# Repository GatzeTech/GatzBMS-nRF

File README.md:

# GatzBMS-nRF

Short explanation for now.

I was a bit annoyed with the Chinese BMS's that you don't have any feedback on the status of for example balancing or why it cutt off power. Once I was in the middle of nowhere when my eBike suddenly stopped and physically I'm really dependant on the electric system so for example in such case, I want to read out the voltage's and decide for myself if it is still safe to go on. If I have to bike myself physically longer distance's (5 km) I can be sick for day's. In that case one cell group was a little bit off, but still in the safe range, in that case I want to be able to put the mosfets on again for example via bluetooth.

So I came up with the idea to design myself a BMS. The goal is to use simple components (also with the chip delivery problems in mind) except for the microcontroller/Soc. It's a compromise between functionality, costs, availability, simplicity.

Design choice's I will discuss later.

At the moment I'm busy with the software.

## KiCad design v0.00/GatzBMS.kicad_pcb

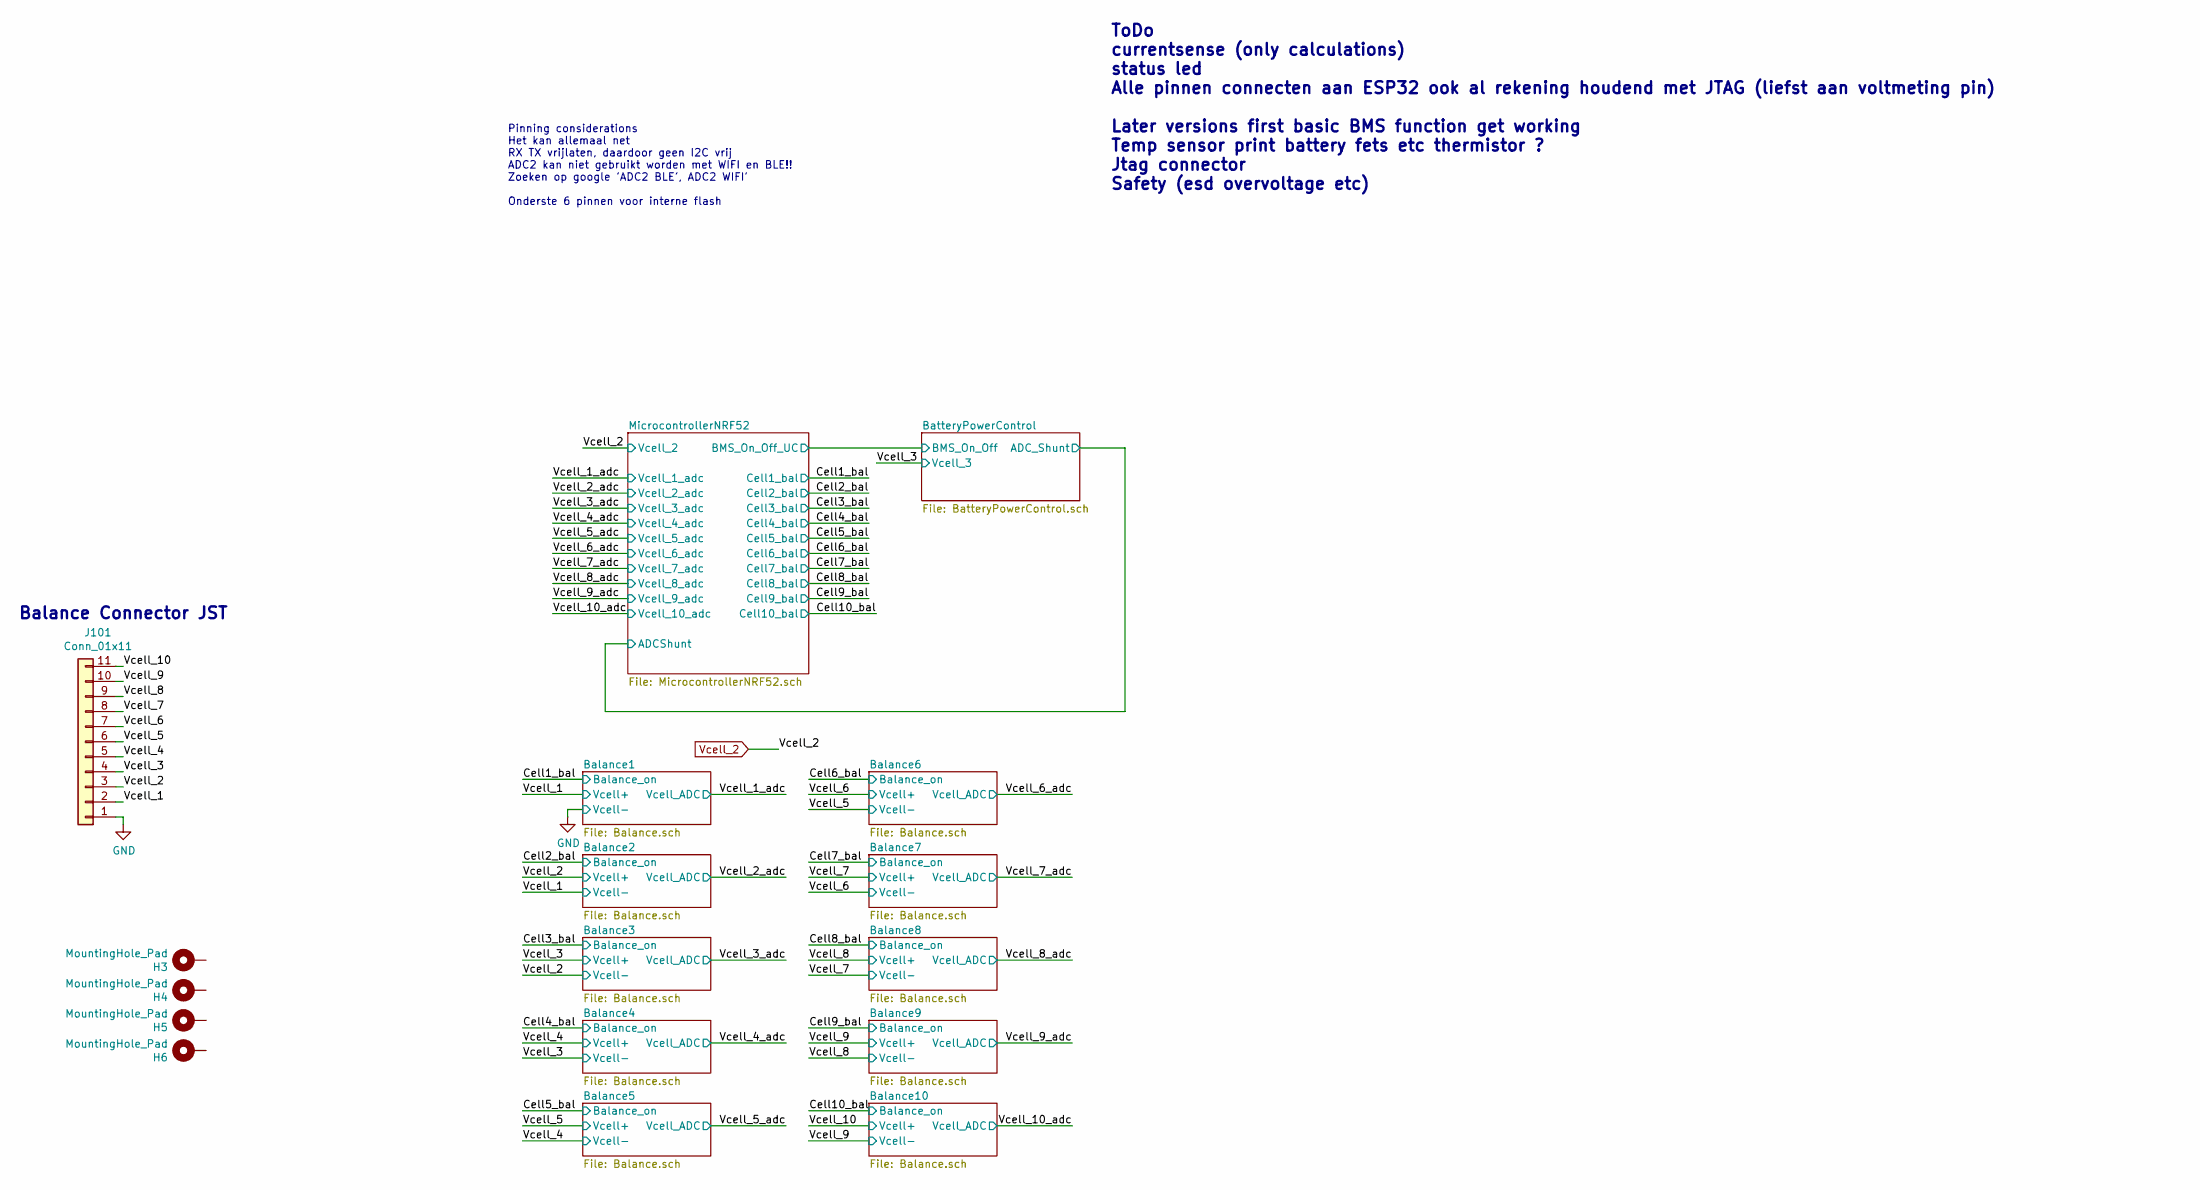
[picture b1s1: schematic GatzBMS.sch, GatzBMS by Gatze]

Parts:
H3, H4, H5, H6: MountingHole_Pad; MountingHole_3.2mm_M3_ISO7380_Pad_TopBottom
J101: Conn_01x11; JST_PH_S11B-PH-K_1x11_P2.00mm_Horizontal

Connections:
/Vcell_1: J101.2; also elsewhere on the board
/Vcell_3: J101.4; also elsewhere on the board
/Vcell_4: J101.5; also elsewhere on the board
/Vcell_5: J101.6; also elsewhere on the board
/Vcell_6: J101.7; also elsewhere on the board
/Vcell_7: J101.8; also elsewhere on the board
/Vcell_8: J101.9; also elsewhere on the board
/Vcell_9: J101.10; also elsewhere on the board
/Vcell_10: J101.11; also elsewhere on the board
GND: J101.1; also elsewhere on the board
Vcell_2: J101.3; also elsewhere on the board

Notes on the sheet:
Balance Connector JST
ToDo currentsense (only calculations) status led Alle pinnen connecten aan ESP32 ook al rekening houdend met JTAG (liefst aan voltmeting pin) Later versions first basic BMS function get working Temp sensor print battery fets etc thermistor ? Jtag connector Safety (esd overvoltage etc)
Pinning considerations Het kan allemaal net RX TX vrijlaten, daardoor geen I2C vrij ADC2 kan niet gebruikt worden met WIFI en BLE!! Zoeken op google 'ADC2 BLE', ADC2 WIFI' Onderste 6 pinnen voor interne flash

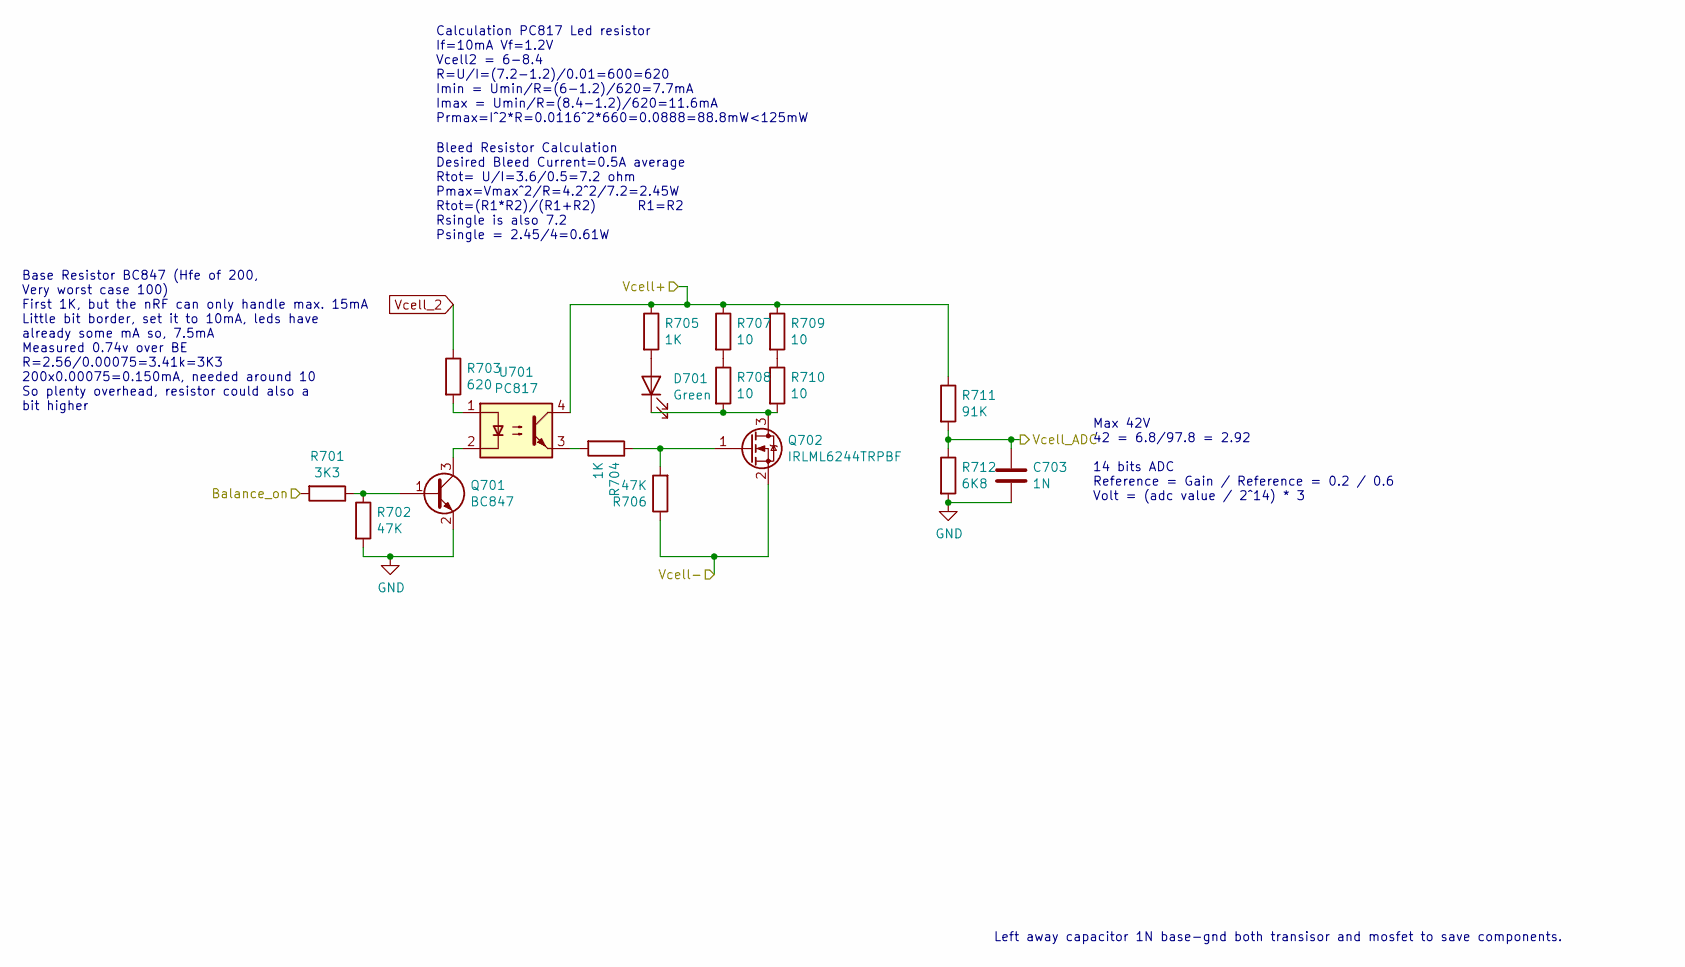
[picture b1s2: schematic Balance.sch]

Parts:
C203: 1N; C_0805_2012Metric
D201: Green; LED_0805_2012Metric_Pad1.15x1.40mm_HandSolder
Q201: BC847; SOT-23
Q202: IRLML6244TRPBF; SOT-23
R201: 3K3; R_0805_2012Metric_Pad1.20x1.40mm_HandSolder
R202, R206: 47K; R_0805_2012Metric_Pad1.20x1.40mm_HandSolder
R203: 620; R_0805_2012Metric_Pad1.20x1.40mm_HandSolder
R204, R205: 1K; R_0805_2012Metric_Pad1.20x1.40mm_HandSolder
R207, R208, R209, R210: 10; R_2512_6332Metric_Pad1.40x3.35mm_HandSolder
R211: 91K; R_0805_2012Metric_Pad1.20x1.40mm_HandSolder
R212: 6K8; R_0805_2012Metric_Pad1.20x1.40mm_HandSolder
U201: PC817; SMDIP-4_W9.53mm_Clearance8mm

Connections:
/Cell1_bal: R201.2; also elsewhere on the board
/Vcell_1: R205.1, R207.1, R209.1, R211.1, U201.4; also elsewhere on the board
/Vcell_1_adc: C203.1, R211.2, R212.1; also elsewhere on the board
GND: C203.2, Q201.2 (E), Q202.2 (S), R202.2, R206.1, R212.2; also elsewhere on the board
unnamed: D201.1 (K), Q202.3 (D), R208.2, R210.2
unnamed: D201.2 (A), R205.2
unnamed: Q201.1 (B), R201.1, R202.1
unnamed: Q201.3 (C), U201.2
unnamed: Q202.1 (G), R204.1, R206.2
unnamed: R203.2, U201.1
unnamed: R204.2, U201.3
unnamed: R207.2, R208.1
unnamed: R209.2, R210.1
Vcell_2: R203.1; also elsewhere on the board

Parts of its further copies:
C303, C403, C503, C603, C703, C803, C903, C1003, C1103: 1N; C_0805_2012Metric
D301, D401, D501, D601, D701, D801, D901, D1001, D1101: Green; LED_0805_2012Metric_Pad1.15x1.40mm_HandSolder
Q301, Q401, Q501, Q601, Q701, Q801, Q901, Q1001, Q1101: BC847; SOT-23
Q302, Q402, Q502, Q602, Q702, Q802, Q902, Q1002, Q1102: IRLML6244TRPBF; SOT-23
R301, R401, R501, R601, R701, R801, R901, R1001, R1101: 3K3; R_0805_2012Metric_Pad1.20x1.40mm_HandSolder
R302, R306, R402, R406, R502, R506, R602, R606, R702, R706, R802, R806, R902, R906, R1002, R1006, R1102, R1106: 47K; R_0805_2012Metric_Pad1.20x1.40mm_HandSolder
R303, R403, R503, R603, R703, R803, R903, R1003, R1103: 620; R_0805_2012Metric_Pad1.20x1.40mm_HandSolder
R304, R305, R404, R405, R504, R505, R604, R605, R704, R705, R804, R805, R904, R905, R1004, R1005, R1104, R1105: 1K; R_0805_2012Metric_Pad1.20x1.40mm_HandSolder
R307, R308, R309, R310, R407, R408, R409, R410, R507, R508, R509, R510, R607, R608, R609, R610, R707, R708, R709, R710, R807, R808, R809, R810, R907, R908, R909, R910, R1007, R1008, R1009, R1010, R1107, R1108, R1109, R1110: 10; R_2512_6332Metric_Pad1.40x3.35mm_HandSolder
R311, R411, R511, R611, R711, R811, R911, R1011, R1111: 91K; R_0805_2012Metric_Pad1.20x1.40mm_HandSolder
R312, R412, R512, R612, R712, R812, R912, R1012, R1112: 6K8; R_0805_2012Metric_Pad1.20x1.40mm_HandSolder
U301, U401, U501, U601, U701, U801, U901, U1001, U1101: PC817; SMDIP-4_W9.53mm_Clearance8mm

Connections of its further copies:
/Cell2_bal: R301.2; also elsewhere on the board
/Cell3_bal: R401.2; also elsewhere on the board
/Cell4_bal: R501.2; also elsewhere on the board
/Cell5_bal: R601.2; also elsewhere on the board
/Cell6_bal: R701.2; also elsewhere on the board
/Cell7_bal: R801.2; also elsewhere on the board
/Cell8_bal: R901.2; also elsewhere on the board
/Cell9_bal: R1001.2; also elsewhere on the board
/Cell10_bal: R1101.2; also elsewhere on the board
/Vcell_1: Q302.2 (S), R306.1; also elsewhere on the board
/Vcell_2_adc: C303.1, R311.2, R312.1; also elsewhere on the board
/Vcell_3: Q502.2 (S), R405.1, R407.1, R409.1, R411.1, R506.1, U401.4; also elsewhere on the board
/Vcell_3_adc: C403.1, R411.2, R412.1; also elsewhere on the board
/Vcell_4: Q602.2 (S), R505.1, R507.1, R509.1, R511.1, R606.1, U501.4; also elsewhere on the board
/Vcell_4_adc: C503.1, R511.2, R512.1; also elsewhere on the board
/Vcell_5: Q702.2 (S), R605.1, R607.1, R609.1, R611.1, R706.1, U601.4; also elsewhere on the board
/Vcell_5_adc: C603.1, R611.2, R612.1; also elsewhere on the board
/Vcell_6: Q802.2 (S), R705.1, R707.1, R709.1, R711.1, R806.1, U701.4; also elsewhere on the board
/Vcell_6_adc: C703.1, R711.2, R712.1; also elsewhere on the board
/Vcell_7: Q902.2 (S), R805.1, R807.1, R809.1, R811.1, R906.1, U801.4; also elsewhere on the board
/Vcell_7_adc: C803.1, R811.2, R812.1; also elsewhere on the board
/Vcell_8: Q1002.2 (S), R905.1, R907.1, R909.1, R911.1, R1006.1, U901.4; also elsewhere on the board
/Vcell_8_adc: C903.1, R911.2, R912.1; also elsewhere on the board
/Vcell_9: Q1102.2 (S), R1005.1, R1007.1, R1009.1, R1011.1, R1106.1, U1001.4; also elsewhere on the board
/Vcell_9_adc: C1003.1, R1011.2, R1012.1; also elsewhere on the board
/Vcell_10: R1105.1, R1107.1, R1109.1, R1111.1, U1101.4; also elsewhere on the board
/Vcell_10_adc: C1103.1, R1111.2, R1112.1; also elsewhere on the board
GND: C303.2, C403.2, C503.2, C603.2, C703.2, C803.2, C903.2, C1003.2, C1103.2, Q301.2 (E), Q401.2 (E), Q501.2 (E), Q601.2 (E), Q701.2 (E), Q801.2 (E), Q901.2 (E), Q1001.2 (E), Q1101.2 (E), R302.2, R312.2, R402.2, R412.2, R502.2, R512.2, R602.2, R612.2, R702.2, R712.2, R802.2, R812.2, R902.2, R912.2, R1002.2, R1012.2, R1102.2, R1112.2; also elsewhere on the board
unnamed: D301.1 (K), Q302.3 (D), R308.2, R310.2
unnamed: D301.2 (A), R305.2
unnamed: D401.1 (K), Q402.3 (D), R408.2, R410.2
unnamed: D401.2 (A), R405.2
unnamed: D501.1 (K), Q502.3 (D), R508.2, R510.2
unnamed: D501.2 (A), R505.2
unnamed: D601.1 (K), Q602.3 (D), R608.2, R610.2
unnamed: D601.2 (A), R605.2
unnamed: D701.1 (K), Q702.3 (D), R708.2, R710.2
unnamed: D701.2 (A), R705.2
unnamed: D801.1 (K), Q802.3 (D), R808.2, R810.2
unnamed: D801.2 (A), R805.2
unnamed: D901.1 (K), Q902.3 (D), R908.2, R910.2
unnamed: D901.2 (A), R905.2
unnamed: D1001.1 (K), Q1002.3 (D), R1008.2, R1010.2
unnamed: D1001.2 (A), R1005.2
unnamed: D1101.1 (K), Q1102.3 (D), R1108.2, R1110.2
unnamed: D1101.2 (A), R1105.2
unnamed: Q301.1 (B), R301.1, R302.1
unnamed: Q301.3 (C), U301.2
unnamed: Q302.1 (G), R304.1, R306.2
unnamed: Q401.1 (B), R401.1, R402.1
unnamed: Q401.3 (C), U401.2
unnamed: Q402.1 (G), R404.1, R406.2
unnamed: Q501.1 (B), R501.1, R502.1
unnamed: Q501.3 (C), U501.2
unnamed: Q502.1 (G), R504.1, R506.2
unnamed: Q601.1 (B), R601.1, R602.1
unnamed: Q601.3 (C), U601.2
unnamed: Q602.1 (G), R604.1, R606.2
unnamed: Q701.1 (B), R701.1, R702.1
unnamed: Q701.3 (C), U701.2
unnamed: Q702.1 (G), R704.1, R706.2
unnamed: Q801.1 (B), R801.1, R802.1
unnamed: Q801.3 (C), U801.2
unnamed: Q802.1 (G), R804.1, R806.2
unnamed: Q901.1 (B), R901.1, R902.1
unnamed: Q901.3 (C), U901.2
unnamed: Q902.1 (G), R904.1, R906.2
unnamed: Q1001.1 (B), R1001.1, R1002.1
unnamed: Q1001.3 (C), U1001.2
unnamed: Q1002.1 (G), R1004.1, R1006.2
unnamed: Q1101.1 (B), R1101.1, R1102.1
unnamed: Q1101.3 (C), U1101.2
unnamed: Q1102.1 (G), R1104.1, R1106.2
unnamed: R303.2, U301.1
unnamed: R304.2, U301.3
unnamed: R307.2, R308.1
unnamed: R309.2, R310.1
unnamed: R403.2, U401.1
unnamed: R404.2, U401.3
unnamed: R407.2, R408.1
unnamed: R409.2, R410.1
unnamed: R503.2, U501.1
unnamed: R504.2, U501.3
unnamed: R507.2, R508.1
unnamed: R509.2, R510.1
unnamed: R603.2, U601.1
unnamed: R604.2, U601.3
unnamed: R607.2, R608.1
unnamed: R609.2, R610.1
unnamed: R703.2, U701.1
unnamed: R704.2, U701.3
unnamed: R707.2, R708.1
unnamed: R709.2, R710.1
unnamed: R803.2, U801.1
unnamed: R804.2, U801.3
unnamed: R807.2, R808.1
unnamed: R809.2, R810.1
unnamed: R903.2, U901.1
unnamed: R904.2, U901.3
unnamed: R907.2, R908.1
unnamed: R909.2, R910.1
unnamed: R1003.2, U1001.1
unnamed: R1004.2, U1001.3
unnamed: R1007.2, R1008.1
unnamed: R1009.2, R1010.1
unnamed: R1103.2, U1101.1
unnamed: R1104.2, U1101.3
unnamed: R1107.2, R1108.1
unnamed: R1109.2, R1110.1
Vcell_2: Q402.2 (S), R303.1, R305.1, R307.1, R309.1, R311.1, R403.1, R406.1, R503.1, R603.1, R703.1, R803.1, R903.1, R1003.1, R1103.1, U301.4; also elsewhere on the board

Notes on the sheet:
Calculation PC817 Led resistor If=10mA Vf=1.2V Vcell2 = 6-8.4 R=U/I=(7.2-1.2)/0.01=600=620 Imin = Umin/R=(6-1.2)/620=7.7mA Imax = Umin/R=(8.4-1.2)/620=11.6mA Prmax=I^2*R=0.0116^2*660=0.0888=88.8mW<125mW
Bleed Resistor Calculation Desired Bleed Current=0.5A average Rtot= U/I=3.6/0.5=7.2 ohm Pmax=Vmax^2/R=4.2^2/7.2=2.45W Rtot=(R1*R2)/(R1+R2) R1=R2 Rsingle is also 7.2 Psingle = 2.45/4=0.61W
Left away capacitor 1N base-gnd both transisor and mosfet to save components.
Base Resistor BC847 (Hfe of 200, Very worst case 100) First 1K, but the nRF can only handle max. 15mA Little bit border, set it to 10mA, leds have already some mA so, 7.5mA Measured 0.74v over BE R=2.56/0.00075=3.41k=3K3 200x0.00075=0.150mA, needed around 10 So plenty overhead, resistor could also 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
Max 42V 42 = 6.8/97.8 = 2.92 14 bits ADC Reference = Gain / Reference = 0.2 / 0.6 Volt = (adc value / 2^14) * 3

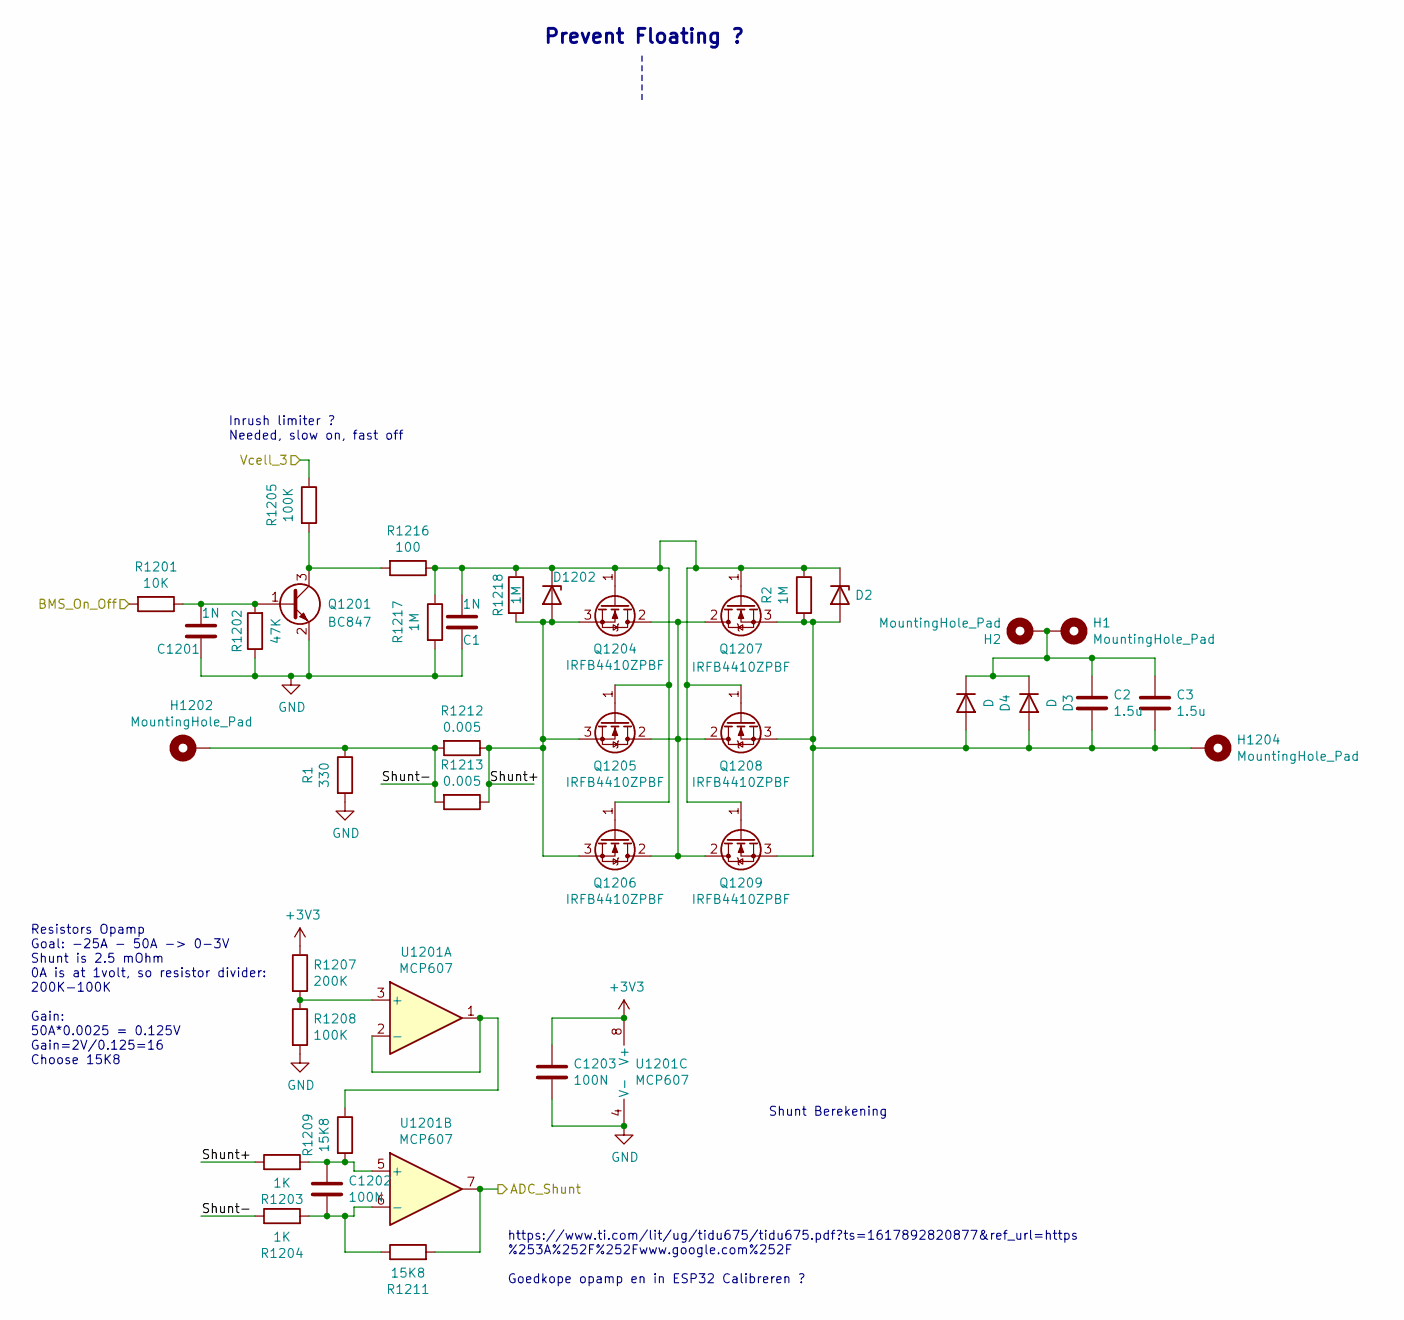
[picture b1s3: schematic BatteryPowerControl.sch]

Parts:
C1, C1201: 1N; C_0805_2012Metric_Pad1.18x1.45mm_HandSolder
C2, C3: 1.5u; C_1210_3225Metric_Pad1.33x2.70mm_HandSolder
C1202, C1203: 100N; C_0805_2012Metric
D2, D1202: Z1SMA15; D_SOD-523
D3, D4: D; D_SMA_Handsoldering
H1, H2, H1202, H1204: MountingHole_Pad; MountingHole_3.2mm_M3_ISO7380_Pad_TopBottom
Q1201: BC847; SOT-23
Q1204, Q1205, Q1206, Q1207, Q1208, Q1209: IRFB4410ZPBF; TO-220-3_Horizontal_TabDown_modified
R1: 330; R_0805_2012Metric_Pad1.20x1.40mm_HandSolder
R2, R1217, R1218: 1M; R_0805_2012Metric_Pad1.20x1.40mm_HandSolder
R1201: 10K; R_0805_2012Metric_Pad1.20x1.40mm_HandSolder
R1202: 47K; R_0805_2012Metric_Pad1.20x1.40mm_HandSolder
R1203, R1204: 1K; R_0805_2012Metric_Pad1.20x1.40mm_HandSolder
R1205, R1208: 100K; R_0805_2012Metric_Pad1.20x1.40mm_HandSolder
R1207: 200K; R_0805_2012Metric_Pad1.20x1.40mm_HandSolder
R1209, R1211: 15K8; R_0805_2012Metric_Pad1.20x1.40mm_HandSolder
R1212, R1213: 0.005; R_2512_6332Metric_Pad1.40x3.35mm_HandSolder
R1216: 100; R_0805_2012Metric_Pad1.20x1.40mm_HandSolder
U1201: MCP607; SOIC-8_3.9x4.9mm_P1.27mm

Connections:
+3V3: C1203.1, R1207.1, U1201.8 (V+); also elsewhere on the board
/BatteryPowerControl/BMS_On_Off: R1201.2; also elsewhere on the board
/BatteryPowerControl/Shunt+: D1202.2 (A), Q1204.3 (S), Q1205.3 (S), Q1206.3 (S), R1203.1, R1212.1, R1213.1, R1218.2
/BatteryPowerControl/Shunt-: H1202.1, R1.1, R1204.1, R1212.2, R1213.2
/MicrocontrollerNRF52/ADCShunt: R1211.2, U1201.7; also elsewhere on the board
/Vcell_3: R1205.1; also elsewhere on the board
GND: C1.2, C1201.2, C1203.2, Q1201.2 (E), R1.2, R1202.1, R1208.2, R1217.2, U1201.4 (V-); also elsewhere on the board
unnamed: C1.1, D2.1 (K), D1202.1 (K), Q1204.1 (G), Q1205.1 (G), Q1206.1 (G), Q1207.1 (G), Q1208.1 (G), Q1209.1 (G), R2.1, R1216.1, R1217.1, R1218.1
unnamed: C2.1, C3.1, D3.1 (K), D4.1 (K), H1.1, H2.1
unnamed: C2.2, C3.2, D2.2 (A), D3.2 (A), D4.2 (A), H1204.1, Q1207.3 (S), Q1208.3 (S), Q1209.3 (S), R2.2
unnamed: C1201.1, Q1201.1 (B), R1201.1, R1202.2
unnamed: C1202.1, R1203.2, R1209.2, U1201.5 (+)
unnamed: C1202.2, R1204.2, R1211.1, U1201.6 (-)
unnamed: Q1201.3 (C), R1205.2, R1216.2
unnamed: Q1204.2 (D), Q1205.2 (D), Q1206.2 (D), Q1207.2 (D), Q1208.2 (D), Q1209.2 (D)
unnamed: R1207.2, R1208.1, U1201.3 (+)
unnamed: R1209.1, U1201.1, U1201.2 (-)

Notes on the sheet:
https://www.ti.com/lit/ug/tidu675/tidu675.pdf?ts=1617892820877&ref_url=https %253A%252F%252Fwww.google.com%252F Goedkope opamp en in ESP32 Calibreren ?
Inrush limiter ? Needed, slow on, fast off
Prevent Floating ?
Shunt Berekening
Resistors Opamp Goal: -25A - 50A -> 0-3V Shunt is 2.5 mOhm 0A is at 1volt, so resistor divider: 200K-100K Gain: 50A*0.0025 = 0.125V Gain=2V/0.125=16 Choose 15K8

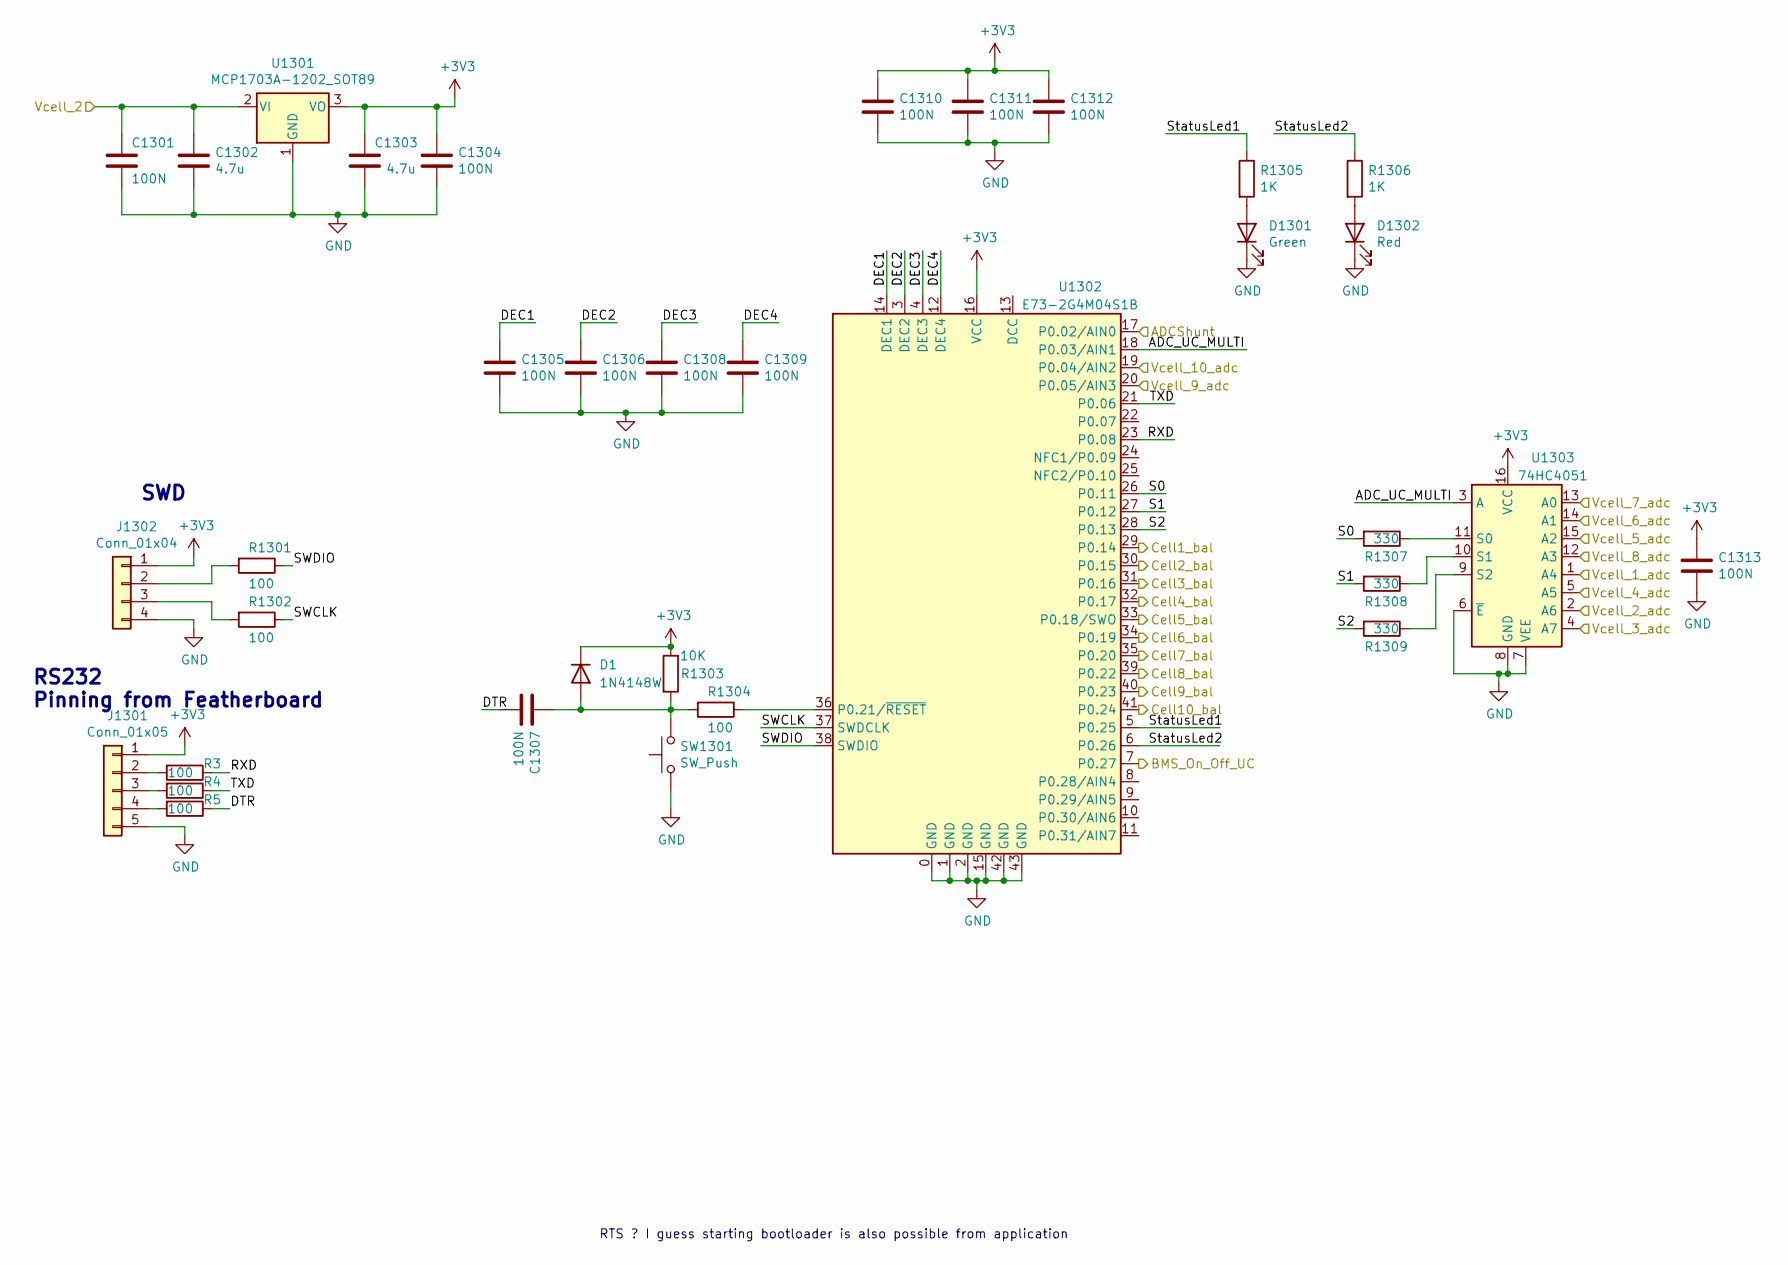
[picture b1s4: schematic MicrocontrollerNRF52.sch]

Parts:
C1301, C1304, C1305, C1306, C1307, C1308, C1309, C1310, C1311, C1312, C1313: 100N; C_0805_2012Metric
C1302, C1303: 4.7u; C_1210_3225Metric_Pad1.33x2.70mm_HandSolder
D1: 1N4148W; D_SOD-123
D1301: Green; LED_0805_2012Metric_Pad1.15x1.40mm_HandSolder
D1302: Red; LED_0805_2012Metric_Pad1.15x1.40mm_HandSolder
J1301: Conn_01x05; JST_PH_B5B-PH-K_1x05_P2.00mm_Vertical
J1302: Conn_01x04; JST_PH_B4B-PH-K_1x04_P2.00mm_Vertical
R3, R4, R5, R1301, R1302, R1304: 100; R_0805_2012Metric_Pad1.20x1.40mm_HandSolder
R1303: 10K; R_0805_2012Metric_Pad1.20x1.40mm_HandSolder
R1305, R1306: 1K; R_0805_2012Metric_Pad1.20x1.40mm_HandSolder
R1307, R1308, R1309: 330; R_0805_2012Metric_Pad1.20x1.40mm_HandSolder
SW1301: SW_Push; SW_Push_1P1T_NO_6x6mm_H9.5mm
U1301: MCP1703A-1202_SOT89; SOT-89-3
U1302: E73-2G4M04S1B
U1303: 74HC4051; SO-16_3.9x9.9mm_P1.27mm

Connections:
+3V3: C1303.1, C1304.1, C1310.1, C1311.1, C1312.1, C1313.1, D1.1 (K), J1301.1, J1302.1, R1303.2, U1301.3 (VO), U1302.16 (VCC), U1303.16 (VCC); also elsewhere on the board
/BatteryPowerControl/BMS_On_Off: U1302.7 (P0.27); also elsewhere on the board
/Cell1_bal: U1302.29 (P0.14); also elsewhere on the board
/Cell2_bal: U1302.30 (P0.15); also elsewhere on the board
/Cell3_bal: U1302.31 (P0.16); also elsewhere on the board
/Cell4_bal: U1302.32 (P0.17); also elsewhere on the board
/Cell5_bal: U1302.33 (P0.18/SWO); also elsewhere on the board
/Cell6_bal: U1302.34 (P0.19); also elsewhere on the board
/Cell7_bal: U1302.35 (P0.20); also elsewhere on the board
/Cell8_bal: U1302.39 (P0.22); also elsewhere on the board
/Cell9_bal: U1302.40 (P0.23); also elsewhere on the board
/Cell10_bal: U1302.41 (P0.24); also elsewhere on the board
/MicrocontrollerNRF52/ADCShunt: U1302.17 (P0.02/AIN0); also elsewhere on the board
/MicrocontrollerNRF52/ADC_UC_MULTI: U1302.18 (P0.03/AIN1), U1303.3 (A)
/MicrocontrollerNRF52/DEC1: C1305.1, U1302.14 (DEC1)
/MicrocontrollerNRF52/DEC2: C1306.1, U1302.3 (DEC2)
/MicrocontrollerNRF52/DEC3: C1308.1, U1302.4 (DEC3)
/MicrocontrollerNRF52/DEC4: C1309.1, U1302.12 (DEC4)
/MicrocontrollerNRF52/DTR: C1307.2, R5.1
/MicrocontrollerNRF52/RXD: R3.1, U1302.23 (P0.08)
/MicrocontrollerNRF52/S0: R1307.2, U1302.26 (P0.11)
/MicrocontrollerNRF52/S1: R1308.2, U1302.27 (P0.12)
/MicrocontrollerNRF52/S2: R1309.2, U1302.28 (P0.13)
/MicrocontrollerNRF52/SWCLK: R1302.1, U1302.37 (SWDCLK)
/MicrocontrollerNRF52/SWDIO: R1301.1, U1302.38 (SWDIO)
/MicrocontrollerNRF52/StatusLed1: R1305.1, U1302.5 (P0.25)
/MicrocontrollerNRF52/StatusLed2: R1306.1, U1302.6 (P0.26)
/MicrocontrollerNRF52/TXD: R4.1, U1302.21 (P0.06)
/Vcell_1_adc: U1303.1 (A4); also elsewhere on the board
/Vcell_2_adc: U1303.2 (A6); also elsewhere on the board
/Vcell_3_adc: U1303.4 (A7); also elsewhere on the board
/Vcell_4_adc: U1303.5 (A5); also elsewhere on the board
/Vcell_5_adc: U1303.15 (A2); also elsewhere on the board
/Vcell_6_adc: U1303.14 (A1); also elsewhere on the board
/Vcell_7_adc: U1303.13 (A0); also elsewhere on the board
/Vcell_8_adc: U1303.12 (A3); also elsewhere on the board
/Vcell_9_adc: U1302.20 (P0.05/AIN3); also elsewhere on the board
/Vcell_10_adc: U1302.19 (P0.04/AIN2); also elsewhere on the board
GND: C1301.2, C1302.2, C1303.2, C1304.2, C1305.2, C1306.2, C1308.2, C1309.2, C1310.2, C1311.2, C1312.2, C1313.2, D1301.1 (K), D1302.1 (K), J1301.5, J1302.4, SW1301.1, U1301.1 (GND), U1302.0 (GND), U1302.1 (GND), U1302.2 (GND), U1302.15 (GND), U1302.42 (GND), U1302.43 (GND), U1303.6 (~E), U1303.7 (VEE), U1303.8 (GND); also elsewhere on the board
unnamed: C1307.1, D1.2 (A), R1303.1, R1304.2, SW1301.2
unnamed: D1301.2 (A), R1305.2
unnamed: D1302.2 (A), R1306.2
unnamed: J1301.2, R3.2
unnamed: J1301.3, R4.2
unnamed: J1301.4, R5.2
unnamed: J1302.2, R1301.2
unnamed: J1302.3, R1302.2
unnamed: R1304.1, U1302.36 (P0.21/~RESET)
unnamed: R1307.1, U1303.11 (S0)
unnamed: R1308.1, U1303.10 (S1)
unnamed: R1309.1, U1303.9 (S2)
Vcell_2: C1301.1, C1302.1, U1301.2 (VI); also elsewhere on the board

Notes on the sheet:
SWD
RS232 Pinning from Featherboard
RTS ? I guess starting bootloader is also possible from application

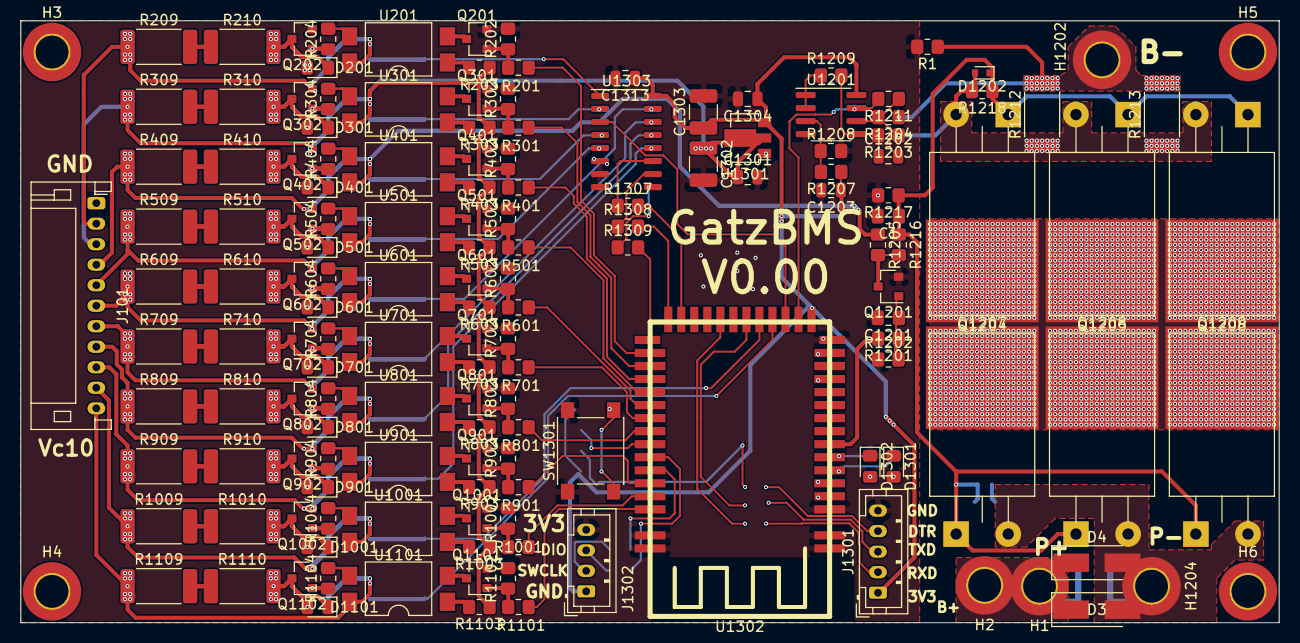
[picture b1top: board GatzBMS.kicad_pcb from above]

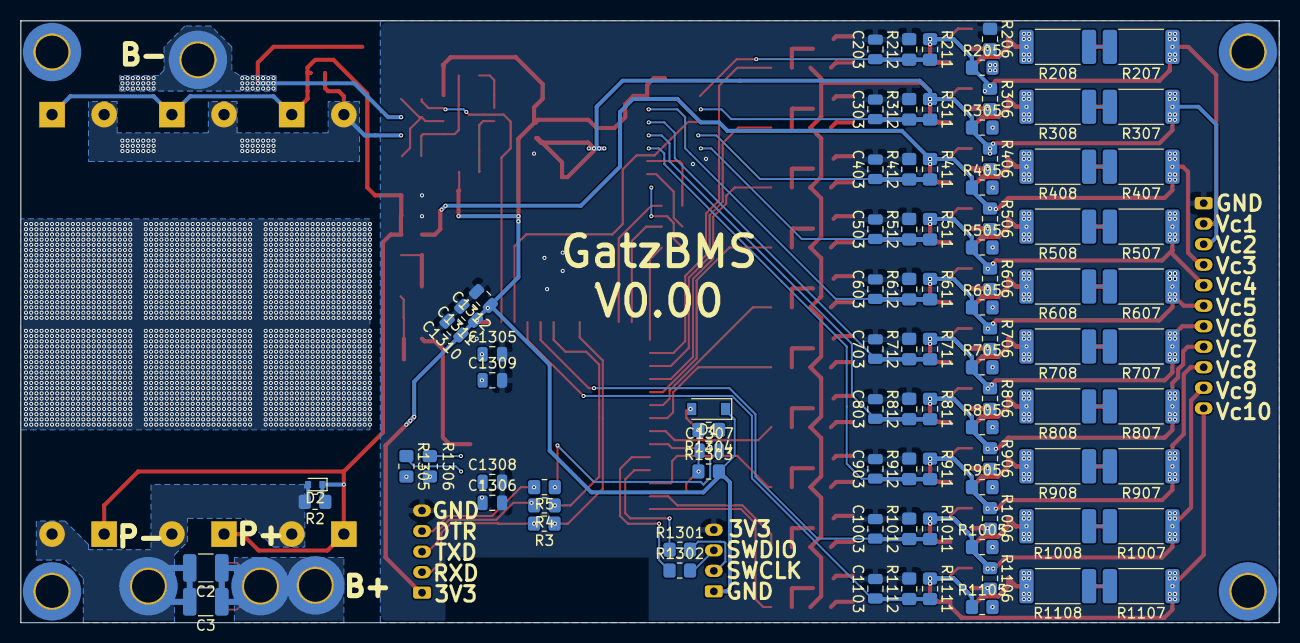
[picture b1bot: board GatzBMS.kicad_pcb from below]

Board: 2 copper layers, 122.7 x 58.7 mm, 247 parts (92 on the bottom side), 163 nets.

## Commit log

2021-11-11 First commits
2021-11-11 Resize images
2021-11-11 Resize
2021-11-11 Rename v0.00/Balance.sch to PCB/Balance.sch
